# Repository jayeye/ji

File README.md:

# JI's stuff

It should be obvious what is mine and what isn't in this repo.

What I've written is licensed under the Beer License (if you found it
useful, buy me a beer when you see me). Feel free to modify or even
sell anything you find in here, just be so kind as to mention me as
the originator. If you can make money out of it, just buy me two beers!

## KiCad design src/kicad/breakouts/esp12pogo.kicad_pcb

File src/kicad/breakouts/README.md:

Hopefully some useful breakout boards here. I trust everyone can figure out what they are for!

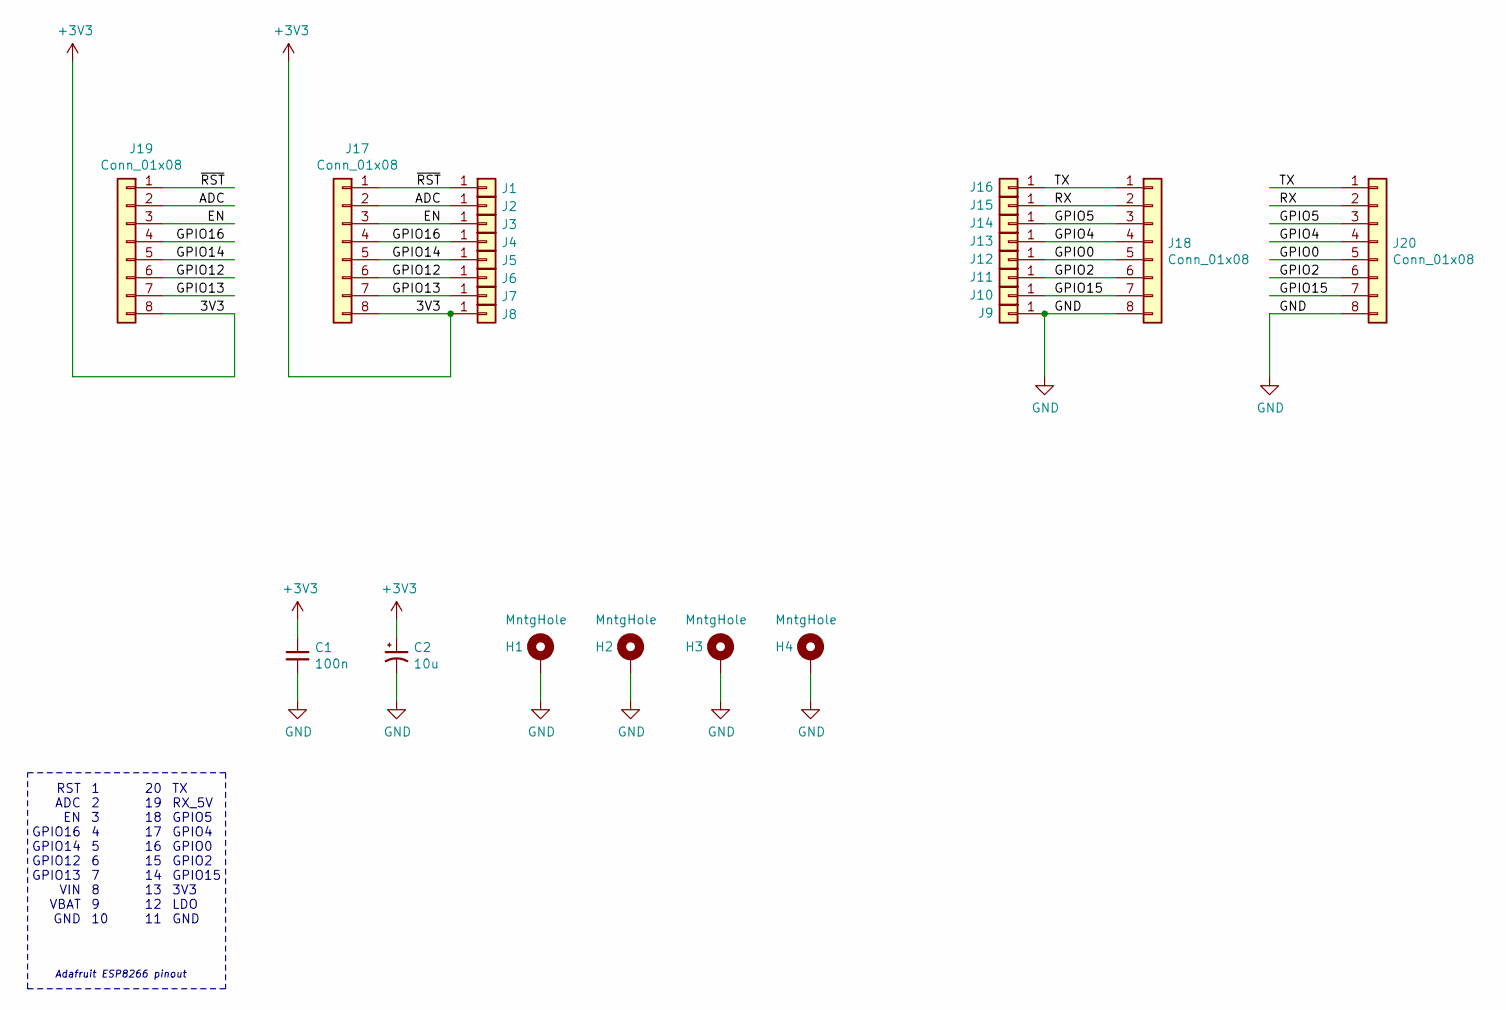
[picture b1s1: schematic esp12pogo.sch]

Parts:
C1: 100n; C_1206_3216Metric
C2: 10u; CP_EIA-3528-12_Kemet-T
H1, H2, H3, H4: MntgHole; MountingHole_3.2mm_M3_ISO14580_Pad
J1, J2, J3, J4, J5, J6, J7, J8, J9, J10, J11, J12, J13, J14, J15, J16: Conn_01x01; pogo
J17, J18, J19, J20: Conn_01x08; PinHeader_1x08_P2.54mm_Vertical

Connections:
+3V3: C1.1, C2.1, J8.1, J17.8, J19.8
/ADC: J2.1, J17.2, J19.2
/EN: J3.1, J17.3, J19.3
/GPIO0: J12.1, J18.5, J20.5
/GPIO2: J11.1, J18.6, J20.6
/GPIO4: J13.1, J18.4, J20.4
/GPIO5: J14.1, J18.3, J20.3
/GPIO12: J6.1, J17.6, J19.6
/GPIO13: J7.1, J17.7, J19.7
/GPIO14: J5.1, J17.5, J19.5
/GPIO15: J10.1, J18.7, J20.7
/GPIO16: J4.1, J17.4, J19.4
/RX: J15.1, J18.2, J20.2
/TX: J16.1, J18.1, J20.1
/~RST: J1.1, J17.1, J19.1
GND: C1.2, C2.2, H1.1, H2.1, H3.1, H4.1, J9.1, J18.8, J20.8

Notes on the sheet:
20 19 18 17 16 15 14 13 12 11
1 2 3 4 5 6 7 8 9 10
TX RX_5V GPIO5 GPIO4 GPIO0 GPIO2 GPIO15 3V3 LDO GND
RST ADC EN GPIO16 GPIO14 GPIO12 GPIO13 VIN VBAT GND
Adafruit ESP8266 pinout

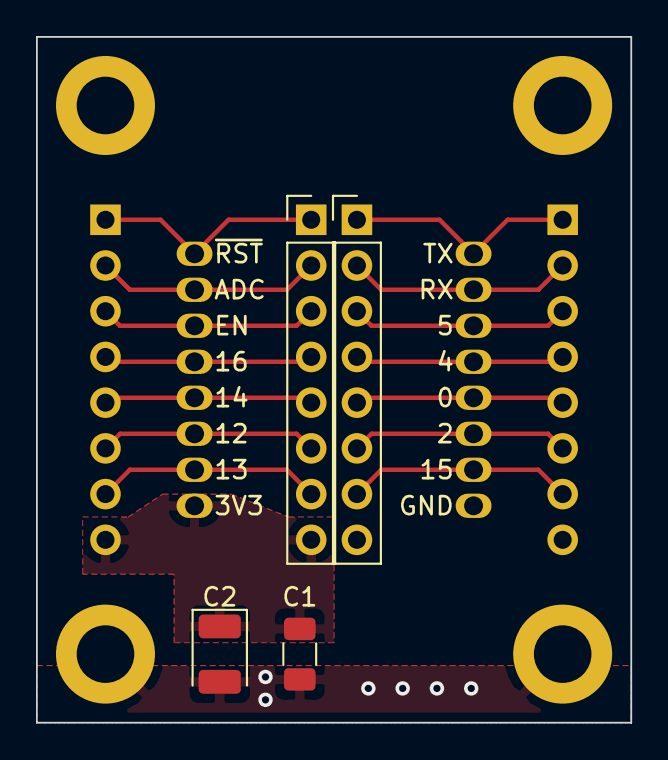
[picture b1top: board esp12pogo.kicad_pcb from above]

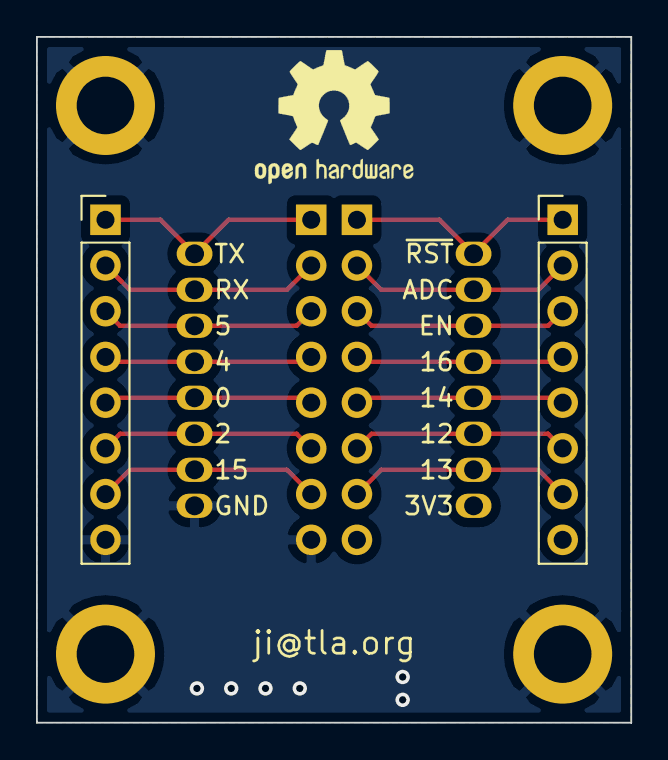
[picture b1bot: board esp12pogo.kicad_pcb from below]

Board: 2 copper layers, 33.0 x 38.1 mm, 26 parts (2 on the bottom side), 16 nets.

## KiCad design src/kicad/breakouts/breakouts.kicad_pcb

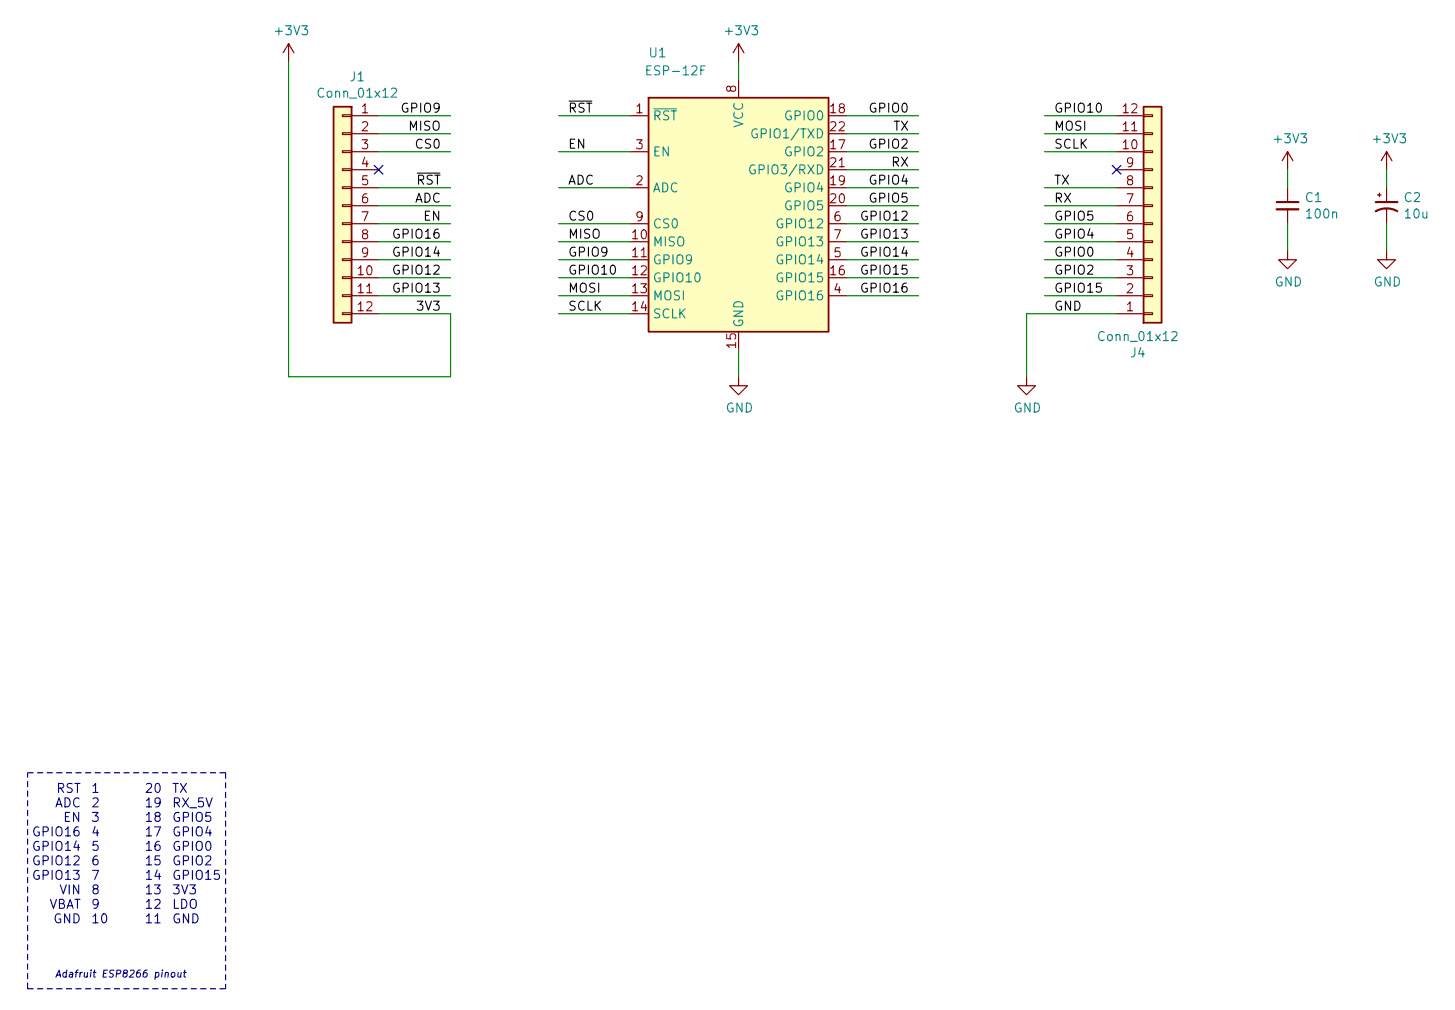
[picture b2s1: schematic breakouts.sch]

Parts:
C1: 100n; C_1206_3216Metric
C2: 10u; CP_EIA-3528-12_Kemet-T
J1, J4: Conn_01x12; PinHeader_1x12_P2.54mm_Vertical
U1: ESP-12F; ESP-12E

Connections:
+3V3: C1.1, C2.1, J1.12, U1.8 (VCC)
/ADC: J1.6, U1.2 (ADC)
/CS0: J1.3, U1.9 (CS0)
/EN: J1.7, U1.3 (EN)
/GPIO0: J4.4, U1.18 (GPIO0)
/GPIO2: J4.3, U1.17 (GPIO2)
/GPIO4: J4.5, U1.19 (GPIO4)
/GPIO5: J4.6, U1.20 (GPIO5)
/GPIO9: J1.1, U1.11 (GPIO9)
/GPIO10: J4.12, U1.12 (GPIO10)
/GPIO12: J1.10, U1.6 (GPIO12)
/GPIO13: J1.11, U1.7 (GPIO13)
/GPIO14: J1.9, U1.5 (GPIO14)
/GPIO15: J4.2, U1.16 (GPIO15)
/GPIO16: J1.8, U1.4 (GPIO16)
/MISO: J1.2, U1.10 (MISO)
/MOSI: J4.11, U1.13 (MOSI)
/RX: J4.7, U1.21 (GPIO3/RXD)
/SCLK: J4.10, U1.14 (SCLK)
/TX: J4.8, U1.22 (GPIO1/TXD)
/~RST: J1.5, U1.1 (~RST)
GND: C1.2, C2.2, J4.1, U1.15 (GND)

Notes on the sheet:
20 19 18 17 16 15 14 13 12 11
1 2 3 4 5 6 7 8 9 10
TX RX_5V GPIO5 GPIO4 GPIO0 GPIO2 GPIO15 3V3 LDO GND
RST ADC EN GPIO16 GPIO14 GPIO12 GPIO13 VIN VBAT GND
Adafruit ESP8266 pinout

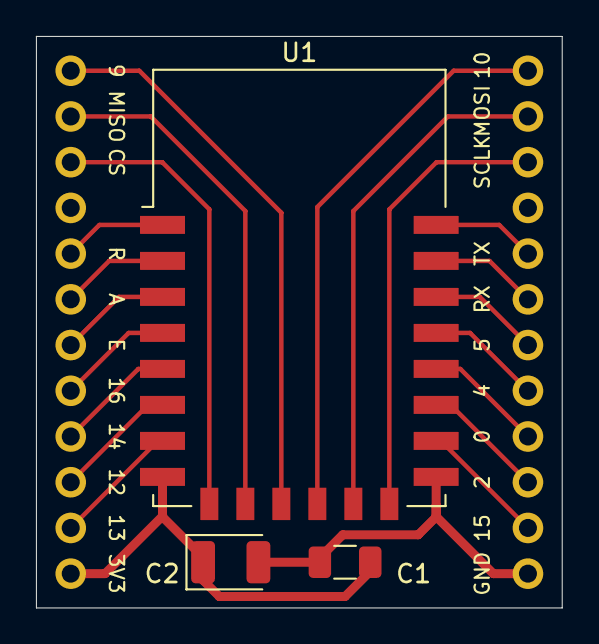
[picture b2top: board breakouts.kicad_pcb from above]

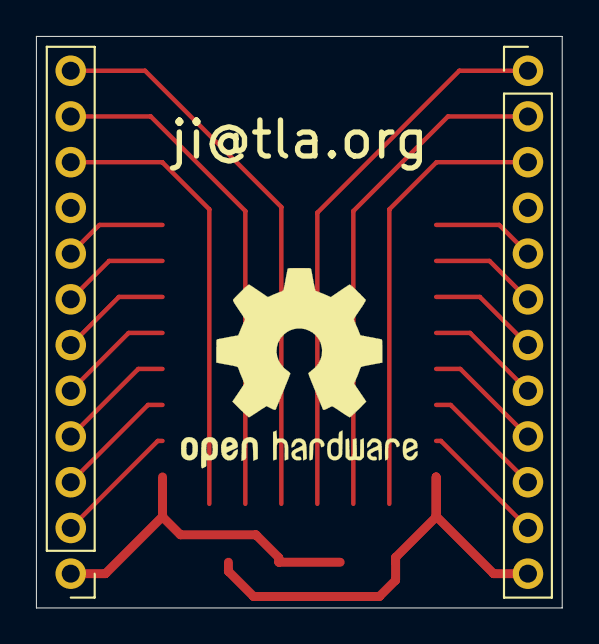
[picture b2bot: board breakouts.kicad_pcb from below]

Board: 2 copper layers, 29.2 x 31.8 mm, 5 parts (2 on the bottom side), 22 nets.

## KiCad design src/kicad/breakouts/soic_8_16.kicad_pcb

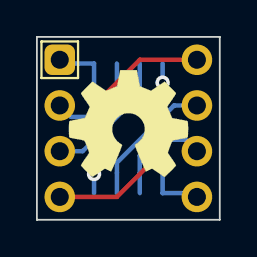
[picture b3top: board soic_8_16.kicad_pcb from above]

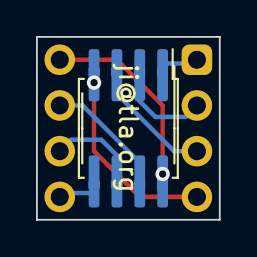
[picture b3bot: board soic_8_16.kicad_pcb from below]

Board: 2 copper layers, 10.2 x 10.2 mm, 3 parts (2 on the bottom side), 8 nets.

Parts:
J1: SOIC-8; SOIC-8_3.9x4.9mm_P1.27mm
J2: SOIC-8; SOIC-8_5.275x5.275mm_P1.27mm
J3: DIP-8; DIP-8-300

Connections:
/D8_1: J1.1, J2.1, J3.1
/D8_2: J1.2, J2.2, J3.2
/D8_3: J1.3, J2.3, J3.3
/D8_4: J1.4, J2.4, J3.4
/D8_5: J1.5, J2.5, J3.5
/D8_6: J1.6, J2.6, J3.6
/D8_7: J1.7, J2.7, J3.7
/D8_8: J1.8, J2.8, J3.8

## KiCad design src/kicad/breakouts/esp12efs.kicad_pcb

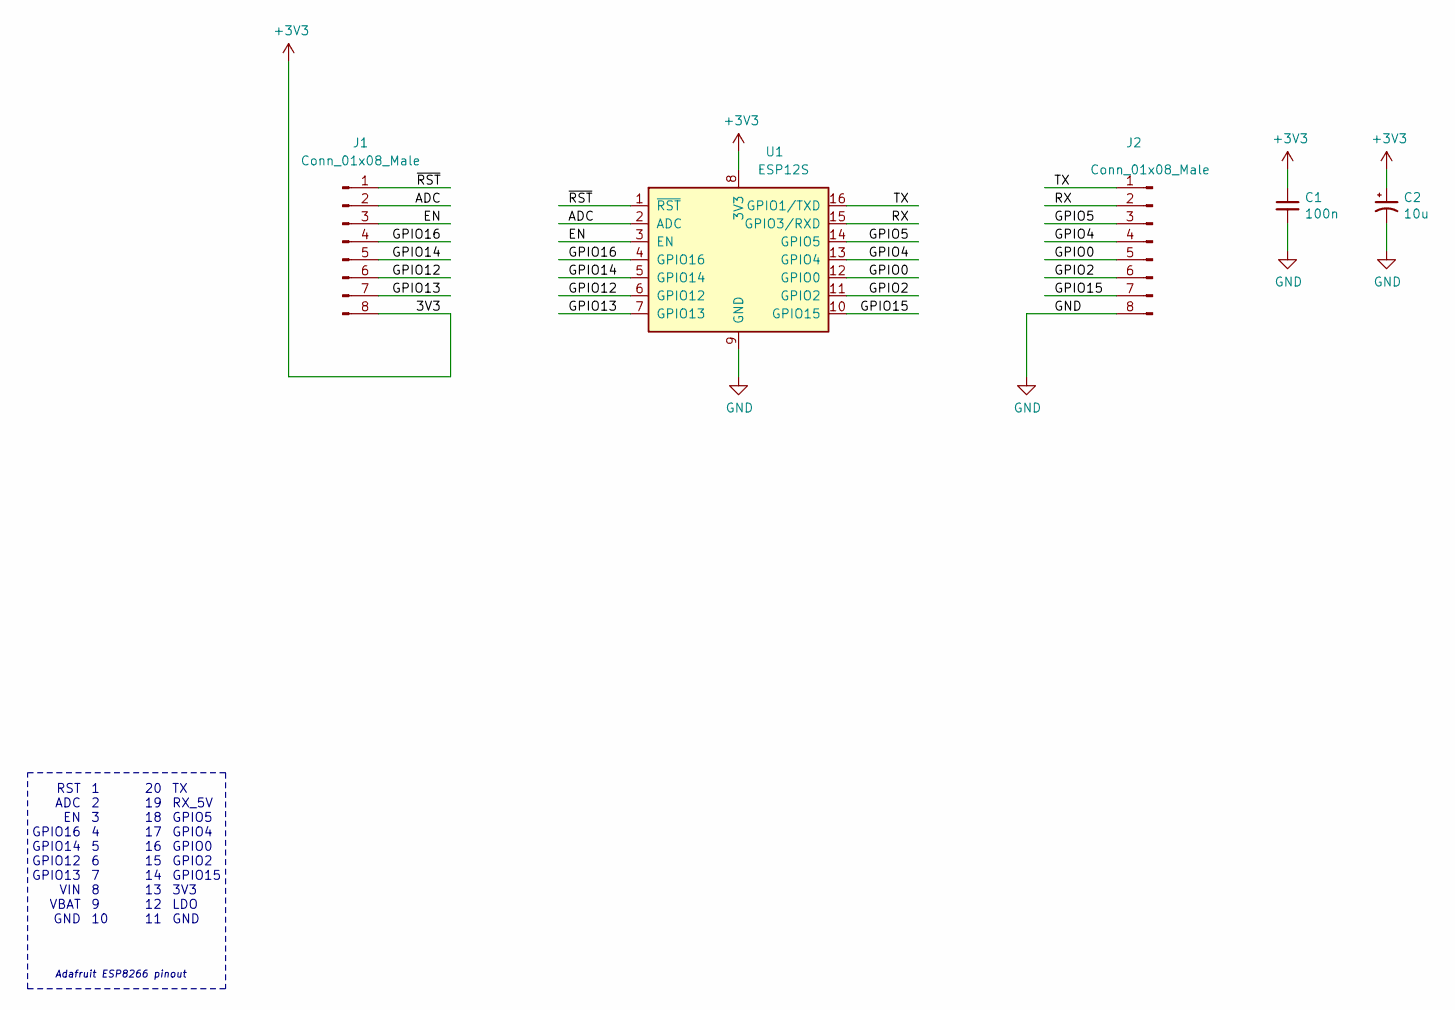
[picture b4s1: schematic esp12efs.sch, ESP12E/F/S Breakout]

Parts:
C1: 100n; C_1206_3216Metric
C2: 10u; CP_EIA-3528-12_Kemet-T
J1, J2: Conn_01x08_Male; PinHeader_1x08_P2.54mm_Vertical
U1: ESP12S

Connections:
+3V3: C1.1, C2.1, J1.8, U1.8 (3V3)
/ADC: J1.2, U1.2 (ADC)
/EN: J1.3, U1.3 (EN)
/GPIO0: J2.5, U1.12 (GPIO0)
/GPIO2: J2.6, U1.11 (GPIO2)
/GPIO4: J2.4, U1.13 (GPIO4)
/GPIO5: J2.3, U1.14 (GPIO5)
/GPIO12: J1.6, U1.6 (GPIO12)
/GPIO13: J1.7, U1.7 (GPIO13)
/GPIO14: J1.5, U1.5 (GPIO14)
/GPIO15: J2.7, U1.10 (GPIO15)
/GPIO16: J1.4, U1.4 (GPIO16)
/RX: J2.2, U1.15 (GPIO3/RXD)
/TX: J2.1, U1.16 (GPIO1/TXD)
/~RST: J1.1, U1.1 (~RST)
GND: C1.2, C2.2, J2.8, U1.9 (GND)

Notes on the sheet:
20 19 18 17 16 15 14 13 12 11
1 2 3 4 5 6 7 8 9 10
TX RX_5V GPIO5 GPIO4 GPIO0 GPIO2 GPIO15 3V3 LDO GND
RST ADC EN GPIO16 GPIO14 GPIO12 GPIO13 VIN VBAT GND
Adafruit ESP8266 pinout

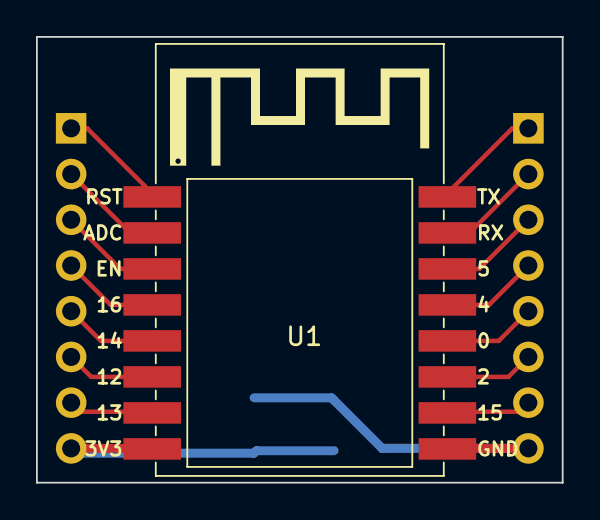
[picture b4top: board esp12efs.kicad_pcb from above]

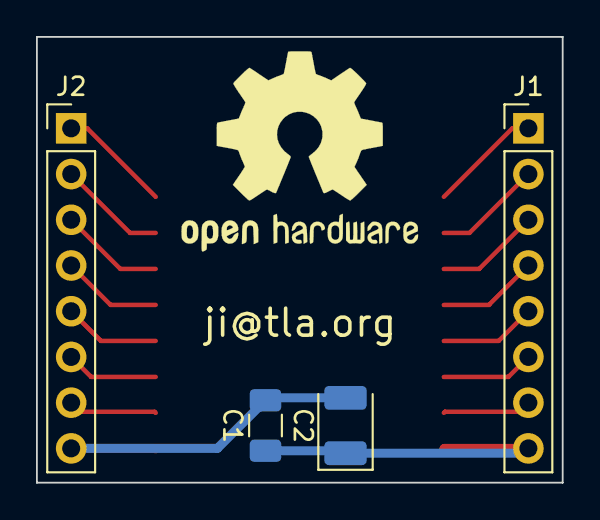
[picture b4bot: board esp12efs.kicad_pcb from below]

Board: 2 copper layers, 29.2 x 24.8 mm, 5 parts (4 on the bottom side), 16 nets.

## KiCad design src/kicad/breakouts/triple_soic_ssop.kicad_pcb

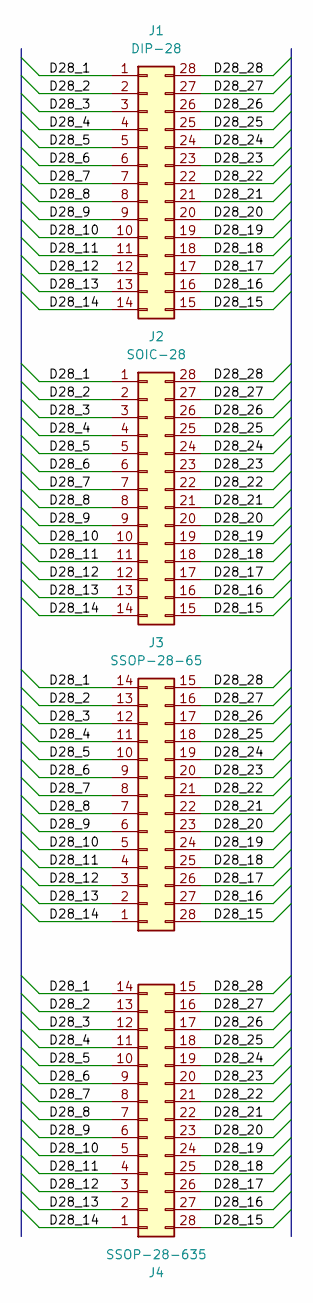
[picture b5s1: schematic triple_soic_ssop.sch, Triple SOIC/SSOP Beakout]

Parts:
J1: DIP-28; DIP-28_700
J2: SOIC-28; SOIC-28W_7.5x17.9mm_P1.27mm
J3: SSOP-28-65; SSOP-28_5.3x10.2mm_P0.65mm
J4: SSOP-28-635; SSOP-28_3.9x9.9mm_P0.635mm

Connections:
/D28_1: J1.1, J2.1, J3.14, J4.14
/D28_2: J1.2, J2.2, J3.13, J4.13
/D28_3: J1.3, J2.3, J3.12, J4.12
/D28_4: J1.4, J2.4, J3.11, J4.11
/D28_5: J1.5, J2.5, J3.10, J4.10
/D28_6: J1.6, J2.6, J3.9, J4.9
/D28_7: J1.7, J2.7, J3.8, J4.8
/D28_8: J1.8, J2.8, J3.7, J4.7
/D28_9: J1.9, J2.9, J3.6, J4.6
/D28_10: J1.10, J2.10, J3.5, J4.5
/D28_11: J1.11, J2.11, J3.4, J4.4
/D28_12: J1.12, J2.12, J3.3, J4.3
/D28_13: J1.13, J2.13, J3.2, J4.2
/D28_14: J1.14, J2.14, J3.1, J4.1
/D28_15: J1.15, J2.15, J3.28, J4.28
/D28_16: J1.16, J2.16, J3.27, J4.27
/D28_17: J1.17, J2.17, J3.26, J4.26
/D28_18: J1.18, J2.18, J3.25, J4.25
/D28_19: J1.19, J2.19, J3.24, J4.24
/D28_20: J1.20, J2.20, J3.23, J4.23
/D28_21: J1.21, J2.21, J3.22, J4.22
/D28_22: J1.22, J2.22, J3.21, J4.21
/D28_23: J1.23, J2.23, J3.20, J4.20
/D28_24: J1.24, J2.24, J3.19, J4.19
/D28_25: J1.25, J2.25, J3.18, J4.18
/D28_26: J1.26, J2.26, J3.17, J4.17
/D28_27: J1.27, J2.27, J3.16, J4.16
/D28_28: J1.28, J2.28, J3.15, J4.15

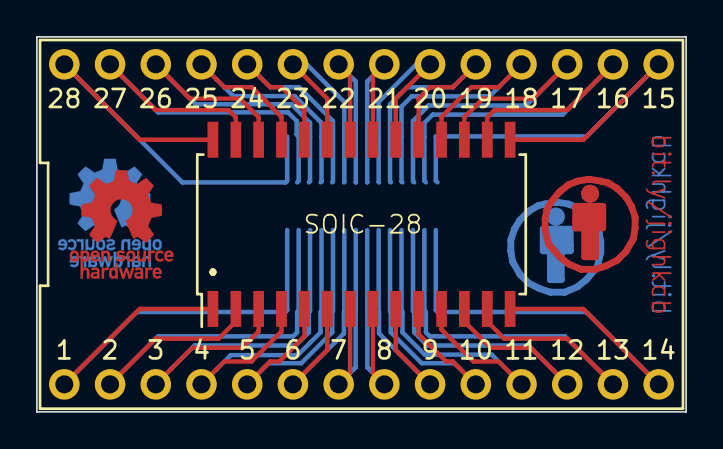
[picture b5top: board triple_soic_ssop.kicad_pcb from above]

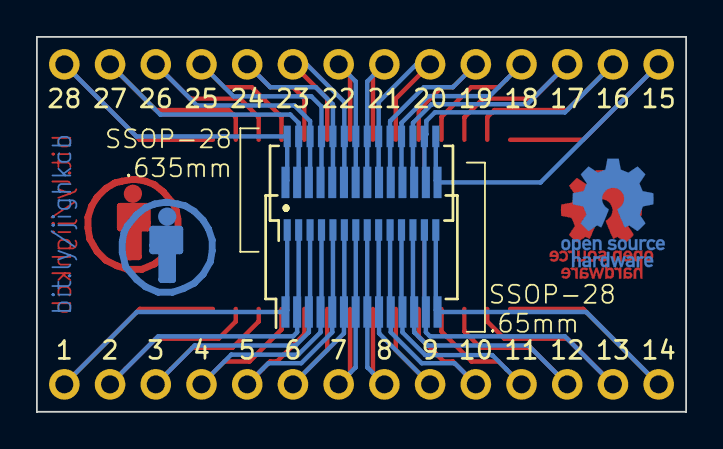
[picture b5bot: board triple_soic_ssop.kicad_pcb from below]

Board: 2 copper layers, 36.1 x 20.8 mm, 4 parts (2 on the bottom side), 28 nets.

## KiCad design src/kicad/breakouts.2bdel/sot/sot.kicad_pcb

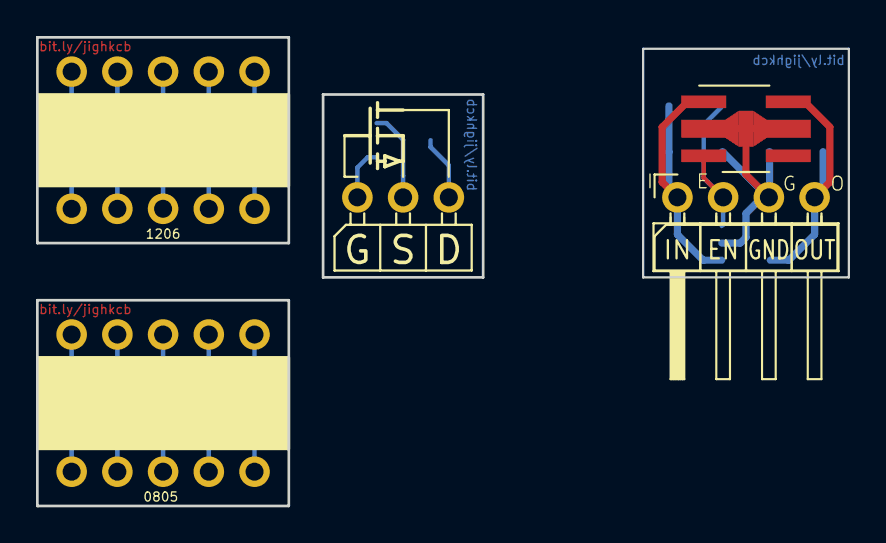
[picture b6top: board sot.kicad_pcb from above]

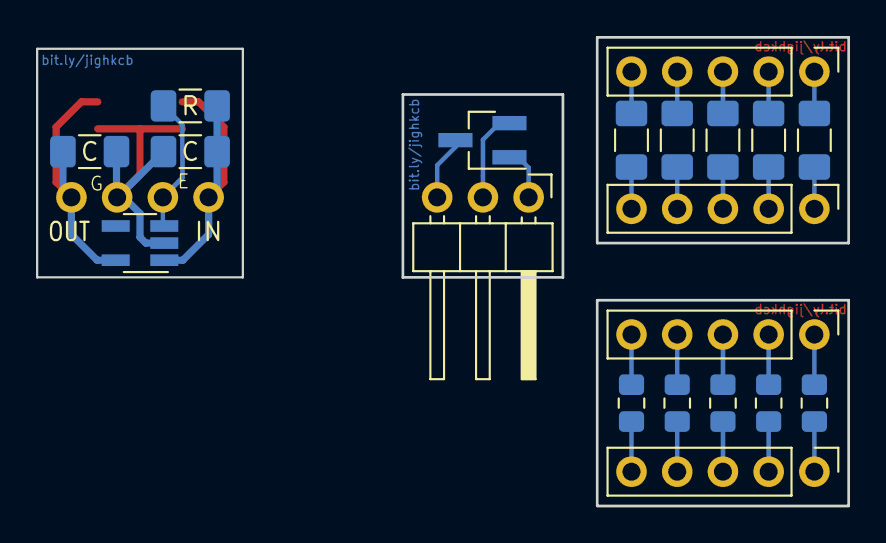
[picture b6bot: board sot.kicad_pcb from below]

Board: 2 copper layers, 45.1 x 26.0 mm, 22 parts (20 on the bottom side), 27 nets.

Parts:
C1, C2: CP; C_1206_3216Metric_Pad1.42x1.75mm_HandSolder
J6, J8, J10, J13: Conn_01x05_Male; PinHeader_1x05_P2.54mm_Vertical
J17: Conn_01x04_Male; PinHeader_1x04_P2.54mm_Horizontal_Left
J18: Conn_01x03_Male; PinHeader_1x03_P2.54mm_Horizontal
Q13: NMOS; SOT-23_Handsoldering
R1, R2, R3, R4, R5, R11: R; R_1206_3216Metric_Pad1.42x1.75mm_HandSolder
R6, R7, R8, R9, R10: R; R_0805_2012Metric_Pad1.15x1.40mm_HandSolder
U1: AP2112K-3.3 SOT-89-5; SOT-89-5_Handsoldering
U2: AP2112K-3.3 SOT-25; SOT-23-5_HandSoldering

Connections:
unnamed: C1.1, J17.1, R11.1, U1.1, U2.1
unnamed: C1.2, C2.2, J17.3, U1.2, U2.2
unnamed: C2.1, J17.4, U1.5, U2.5
unnamed: J6.1, R1.1
unnamed: J6.2, R2.1
unnamed: J6.3, R3.1
unnamed: J6.4, R4.1
unnamed: J6.5, R5.1
unnamed: J8.1, R1.2
unnamed: J8.2, R2.2
unnamed: J8.3, R3.2
unnamed: J8.4, R4.2
unnamed: J8.5, R5.2
unnamed: J10.1, R6.1
unnamed: J10.2, R7.1
unnamed: J10.3, R8.1
unnamed: J10.4, R9.1
unnamed: J10.5, R10.1
unnamed: J13.1, R6.2
unnamed: J13.2, R7.2
unnamed: J13.3, R8.2
unnamed: J13.4, R9.2
unnamed: J13.5, R10.2
unnamed: J17.2, R11.2, U1.3, U2.3
unnamed: J18.1, Q13.1
unnamed: J18.2, Q13.2
unnamed: J18.3, Q13.3

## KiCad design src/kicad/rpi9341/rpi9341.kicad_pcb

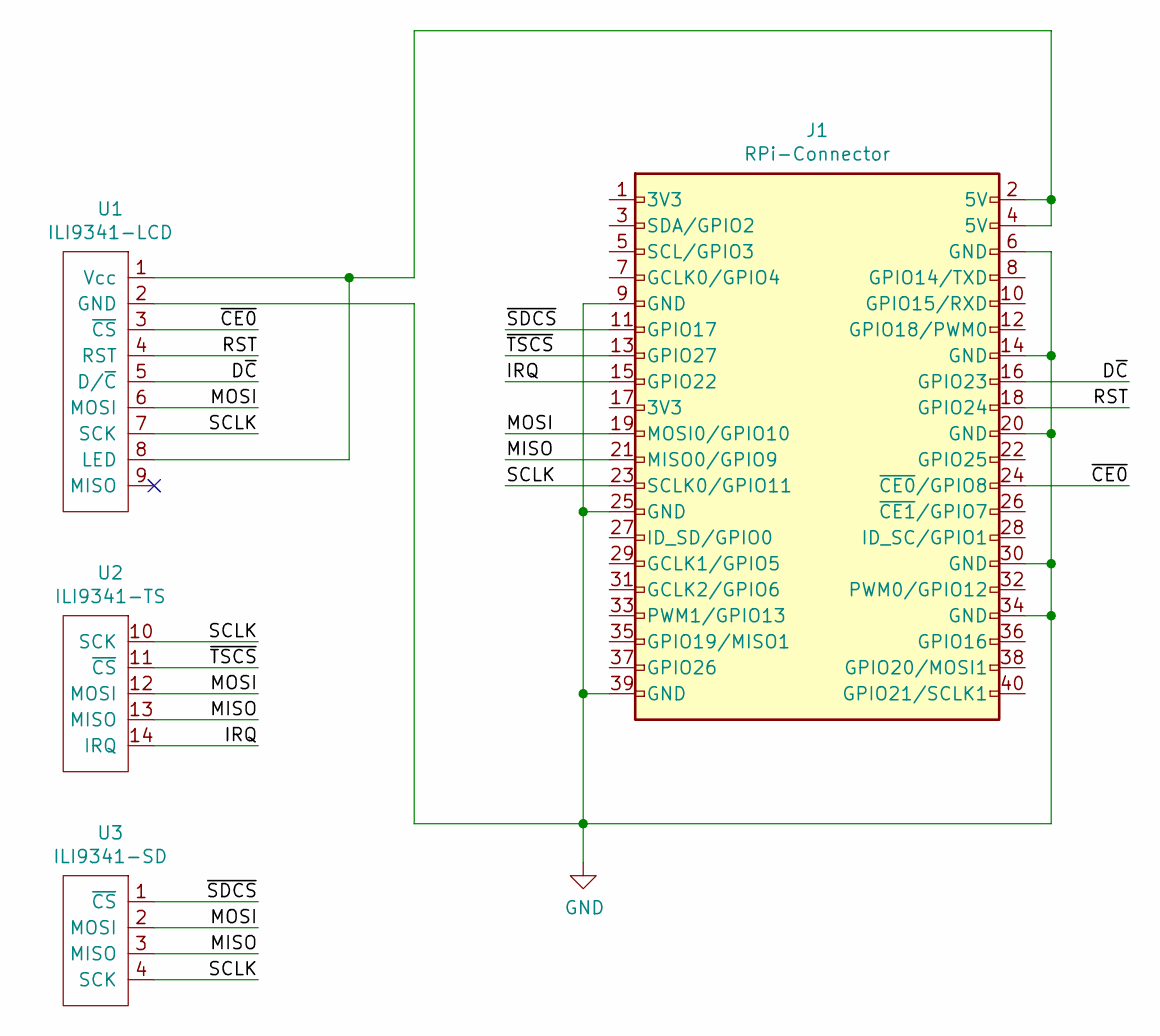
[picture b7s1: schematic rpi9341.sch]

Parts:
J1: RPi-Connector; PinSocket_2x20_P2.54mm_Vertical
U1: ILI9341-LCD; PinSocket_1x09_P2.54mm_Vertical
U2: ILI9341-TS; PinSocket_1x05_P2.54mm_Vertical
U3: ILI9341-SD; PinSocket_1x04_P2.54mm_Vertical

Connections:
/D~C: J1.16 (GPIO23), U1.5 (D/~C)
/IRQ: J1.15 (GPIO22), U2.14 (IRQ)
/MISO: J1.21 (MISO0/GPIO9), U2.13 (MISO), U3.3 (MISO)
/MOSI: J1.19 (MOSI0/GPIO10), U1.6 (MOSI), U2.12 (MOSI), U3.2 (MOSI)
/RST: J1.18 (GPIO24), U1.4 (RST)
/SCLK: J1.23 (SCLK0/GPIO11), U1.7 (SCK), U2.10 (SCK), U3.4 (SCK)
/~CE0: J1.24 (~CE0~/GPIO8), U1.3 (~CS)
/~SDCS: J1.11 (GPIO17), U3.1 (~CS)
/~TSCS: J1.13 (GPIO27), U2.11 (~CS)
GND: J1.6 (GND), J1.9 (GND), J1.14 (GND), J1.20 (GND), J1.25 (GND), J1.30 (GND), J1.34 (GND), J1.39 (GND), U1.2 (GND)
unnamed: J1.2 (5V), J1.4 (5V), U1.1 (Vcc), U1.8 (LED)

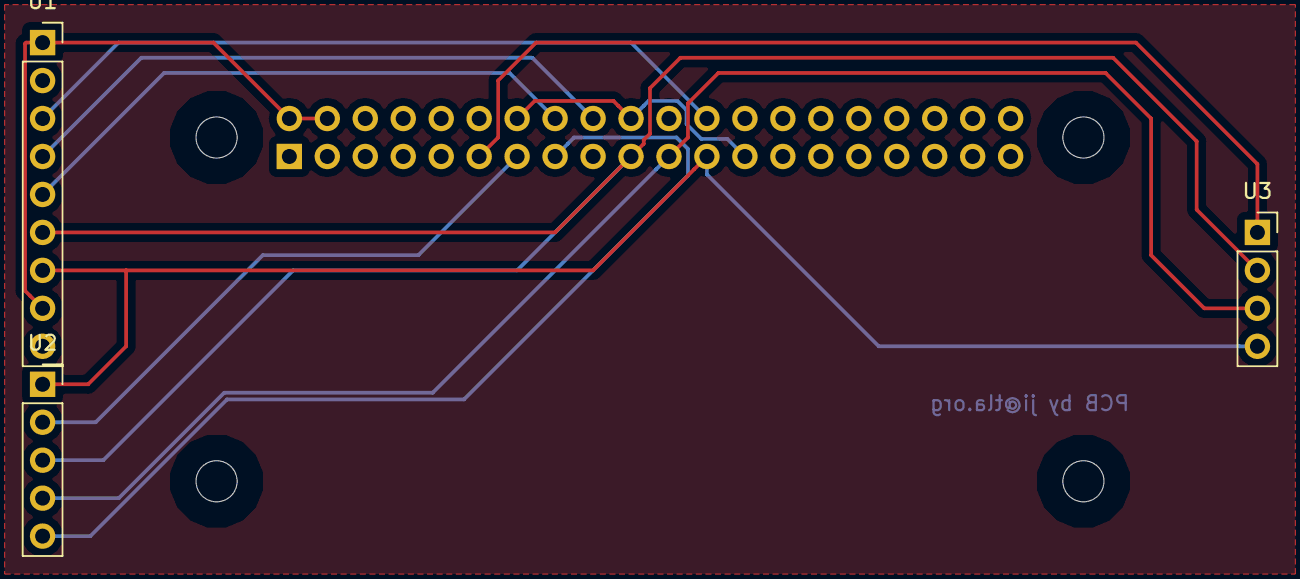
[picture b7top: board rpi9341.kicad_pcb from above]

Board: 2 copper layers, 6 parts (1 on the bottom side), 11 nets.

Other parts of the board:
H1, H2: MountingHole; tiedown

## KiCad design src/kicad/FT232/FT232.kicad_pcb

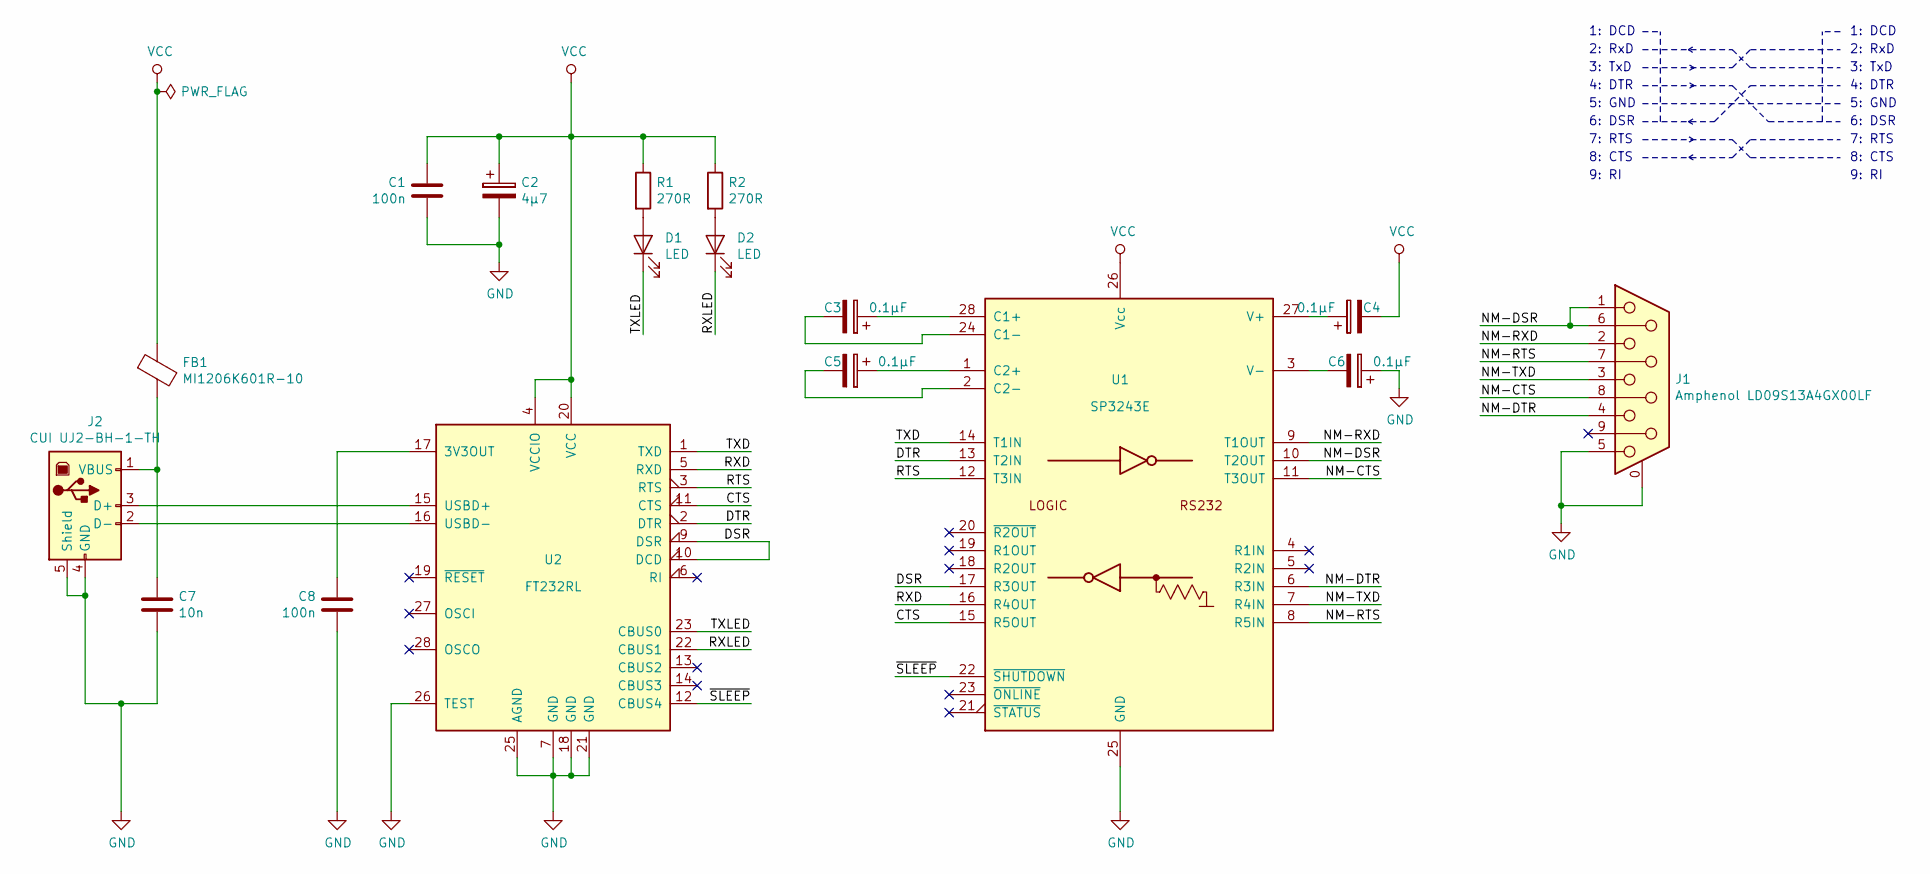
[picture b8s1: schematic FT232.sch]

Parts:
C1, C8: 100n; C_0805_2012Metric_Pad1.15x1.40mm_HandSolder
C2: 4μ7; CP_EIA-3216-12_Kemet-S_Pad1.58x1.35mm_HandSolder
C3, C4, C5, C6: 0.1μF; CP_EIA-2012-12_Kemet-R_Pad1.30x1.05mm_HandSolder
C7: 10n; C_0805_2012Metric_Pad1.15x1.40mm_HandSolder
D1, D2: LED; LED_0805_2012Metric_Pad1.15x1.40mm_HandSolder
FB1: MI1206K601R-10; R_1206_3216Metric_Pad1.42x1.75mm_HandSolder
J1: Amphenol LD09S13A4GX00LF; DSUB-9_Female_Horizontal_P2.77x2.84mm_EdgePinOffset9.90mm_H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
J2: CUI UJ2-BH-1-TH; CUI-UJ2-BH-1-TH
R1, R2: 270R; R_0805_2012Metric_Pad1.15x1.40mm_HandSolder
U1: SP3243E; SSOP-28_5.3x10.2mm_P0.65mm
U2: FT232RL; SSOP-28_5.3x10.2mm_P0.65mm

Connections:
/CTS: U1.15 (R5OUT), U2.11 (CTS)
/DSR: U1.17 (R3OUT), U2.9 (DSR), U2.10 (DCD)
/DTR: U1.13 (T2IN), U2.2 (DTR)
/NM-CTS: J1.8, U1.11 (T3OUT)
/NM-DSR: J1.1, J1.6, U1.10 (T2OUT)
/NM-DTR: J1.4, U1.6 (R3IN)
/NM-RTS: J1.7, U1.8 (R5IN)
/NM-RXD: J1.2, U1.9 (T1OUT)
/NM-TXD: J1.3, U1.7 (R4IN)
/RTS: U1.12 (T3IN), U2.3 (RTS)
/RXD: U1.16 (R4OUT), U2.5 (RXD)
/RXLED: D2.1 (K), U2.22 (CBUS1)
/TXD: U1.14 (T1IN), U2.1 (TXD)
/TXLED: D1.1 (K), U2.23 (CBUS0)
/~SLEEP: U1.22 (~SHUTDOWN), U2.12 (CBUS4)
GND: C1.2, C2.2, C6.1, C7.2, C8.2, J1.0 (PAD), J1.5, J2.4 (GND), J2.5 (Shield), U1.25 (GND), U2.7 (GND), U2.18 (GND), U2.21 (GND), U2.25 (AGND), U2.26 (TEST)
unnamed: C3.1, U1.28 (C1+)
unnamed: C3.2, U1.24 (C1-)
unnamed: C4.1, U1.27 (V+)
unnamed: C5.1, U1.1 (C2+)
unnamed: C5.2, U1.2 (C2-)
unnamed: C6.2, U1.3 (V-)
unnamed: C7.1, FB1.2, J2.1 (VBUS)
unnamed: C8.1, U2.17 (3V3OUT)
unnamed: D1.2 (A), R1.2
unnamed: D2.2 (A), R2.2
unnamed: J2.2 (D-), U2.16 (USBD-)
unnamed: J2.3 (D+), U2.15 (USBD+)
VCC: C1.1, C2.1, C4.2, FB1.1, R1.1, R2.1, U1.26 (Vcc), U2.4 (VCCIO), U2.20 (VCC)

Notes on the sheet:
1: DCD
2: RxD
3: TxD
4: DTR
5: GND
6: DSR
7: RTS
8: CTS
9: RI
